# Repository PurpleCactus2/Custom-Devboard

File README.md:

# Custom-Devboard
An RP2040 devboard meant for a completely custom and streamlined electronics development experience!

## Introduction
This is a completely custom devboard made with the wonderful guide by [@Kai Pereira](https://blueprint.hackclub.com/starter-projects/devboard)

It features:

- An RP2040 microcontroller
- All 30 GPIO pins of the RP2040 broken out, with plently power and debugging pins as well
- 2MB of flash storage

## PCB and Schematic

### Schematic
My schematic uses a mostly similar layout to the one suggested in the guide, however, I have also included a diode and VSYS pin so that you can connect an external battery/power source to power the board. In addition to this, I have also changed the external pin layout a little in a way that makes more sense to me, but you'll see what I mean.

Here are a couple of screenshots of the schematic:

The RP2040 with its decoupling capacitors:<br>
<br>

The USB-C port (you can also see the diode I added here):<br>
<br>

The flash memory along with the BOOTSEL button:<br>
<br>

The 12MHz crystal oscillator:<br>
<br>

The IO pins with a slightly changed layout:<br>
<br>

### PCB
This is my first time using SMD so my layout and routing are a little atrocious. But I have tried my best to keep everything as logical as possible.

Here are a couple screenshots of the PCB:

The RP2040 footprint with decoupling caps, crystal and flash:<br>
<br>

The whole board:<br>
<br>

Final render:<br>
<br>

## BOM
|  | Item | Qty | Supplier | Cost/item | Total Cost | link |
|---|---|---|---|---|---|---|
|  | RP2040 | 1 | LCSC | $1.10 | $1.10 | [LCSC](https://www.lcsc.com/product-detail/C2040.html) |
|  | MCP1700 | 1 | LCSC | $0.44 | $0.44 | [LCSC](https://www.lcsc.com/product-detail/C39051.html) |
|  | Crystal | 1 | LCSC | $0.46 | $0.46 | [LCSC](https://www.lcsc.com/product-detail/C9002.html) |
|  | Flash memory | 1 | LCSC | $1.92 | $1.92 | [LCSC](https://www.lcsc.com/product-detail/C2456208.html) |
|  | Button | 1 | LCSC | $0.51 | $0.51 | [LCSC](https://www.lcsc.com/product-detail/C720477.html) |
|  | USB-C Port | 1 | LCSC | $0.87 | $0.87 | [LCSC](https://www.lcsc.com/product-detail/C165948.html) |
|  | Passive Components | 1 | LCSC | $1.57 | $1.57 | [100nF](https://www.lcsc.com/product-detail/C1525.html) [1uF](https://www.lcsc.com/product-detail/C2803380.html) [10uF](https://www.lcsc.com/product-detail/C1691.html) [33pF](https://www.lcsc.com/product-detail/C107005.html) [Diode](https://www.lcsc.com/product-detail/C49231016.html) [5.1KΩ](https://www.lcsc.com/product-detail/C2906874.html) [27Ω](https://www.lcsc.com/product-detail/C2909343.html) [1KΩ](https://www.lcsc.com/product-detail/C2906899.html) [10KΩ](https://www.lcsc.com/product-detail/C2906861.html) |
|  | PCB | 1 | JLCPCB | $4.10 | $4.10 | [LCSC](https://cart.jlcpcb.com/quote?stencilLayer=2&stencilWiddth=100&stencilLength=100&stencilCounts=5&plateType=1&spm=Jlcpcb.Homepage.1010) |
|  | Estimated total shipping |  |  |  | $18.94 |  |
|  | Total |  |  |  | $29.91 |  |

*I am willing to cover any extra charges that might apply*

### Cart Screenshots

LCSC Order:<br>
<br>
<br>
<br>

JLCPCB Order:<br>

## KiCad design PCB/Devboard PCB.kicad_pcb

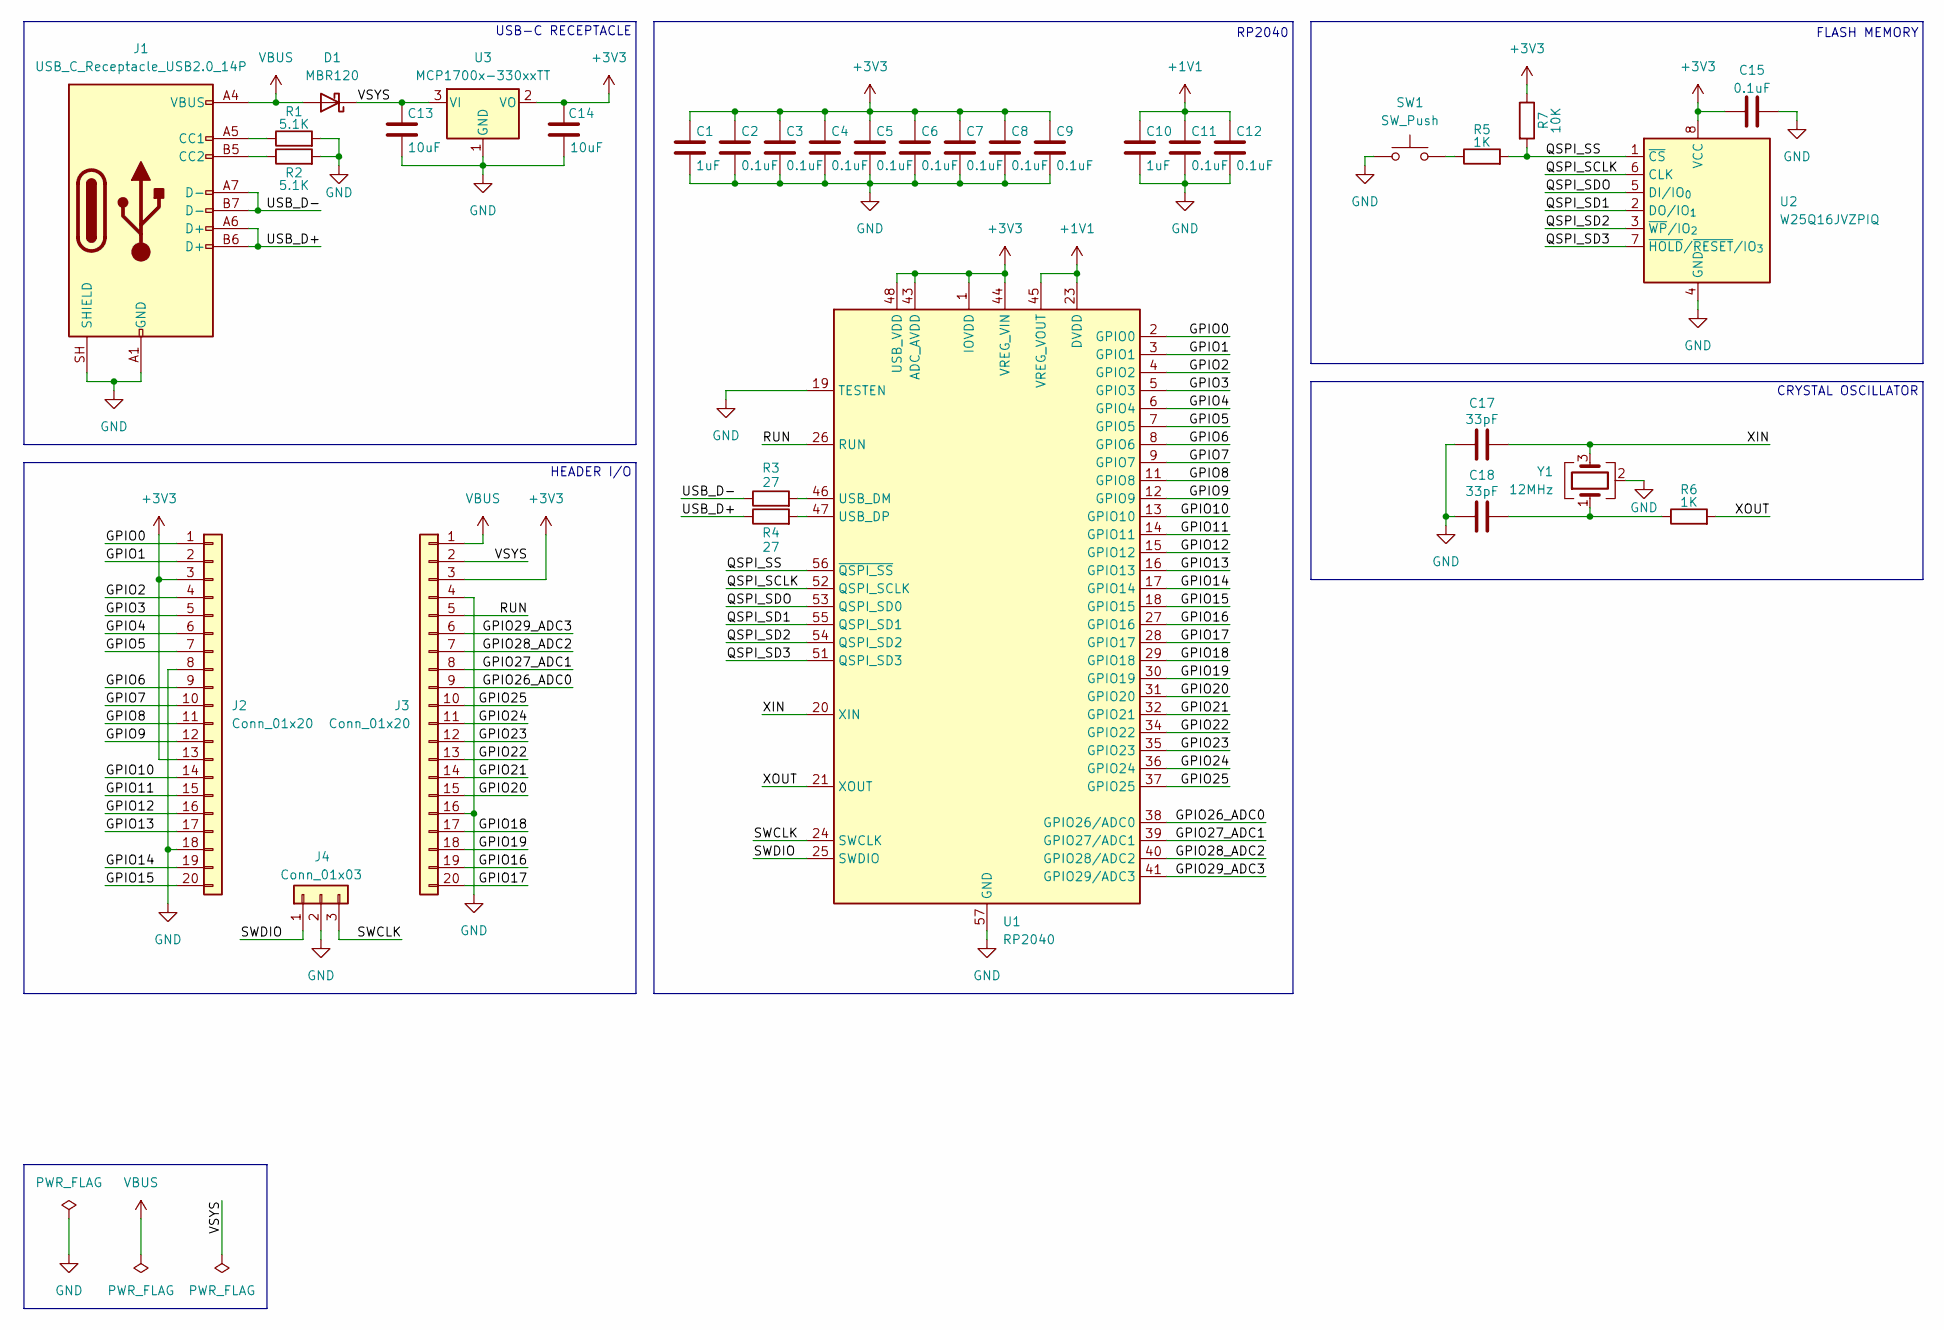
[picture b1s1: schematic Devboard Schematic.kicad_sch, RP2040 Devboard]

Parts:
C1, C10: 1uF; C_0402_1005Metric
C2, C3, C4, C5, C6, C7, C8, C9, C11, C12, C15: 0.1uF; C_0402_1005Metric
C13, C14: 10uF; C_0603_1608Metric
C17, C18: 33pF; C_0402_1005Metric
D1: MBR120; D_SOD-123F
J1: USB_C_Receptacle_USB2.0_14P; USB_C_Receptacle_HRO_TYPE-C-31-M-12
J2, J3: Conn_01x20; PinHeader_1x20_P2.54mm_Vertical
J4: Conn_01x03; PinHeader_1x03_P2.54mm_Vertical
R1, R2: 5.1K; R_01005_0402Metric
R3, R4: 27; R_01005_0402Metric
R5, R6: 1K; R_01005_0402Metric
R7: 10K; R_01005_0402Metric
SW1: SW_Push; SW_Push_SPST_NO_Alps_SKRK
U1: RP2040; QFN-56-1EP_7x7mm_P0.4mm_EP3.2x3.2mm
U2: W25Q16JVZPIQ; Winbond_USON-8-1EP_3x2mm_P0.5mm_EP0.2x1.6mm
U3: MCP1700x-330xxTT; SOT-23
Y1: 12MHz; Crystal_SMD_3225-4Pin_3.2x2.5mm

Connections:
+1V1: C10.1, C11.1, C12.1, U1.23 (DVDD), U1.45 (VREG_VOUT), U1.50 (DVDD)
+3V3: C1.1, C2.1, C3.1, C4.1, C5.1, C6.1, C7.1, C8.1, C9.1, C14.1, C15.1, J2.3, J2.13, J3.3, R7.1, U1.1 (IOVDD), U1.10 (IOVDD), U1.22 (IOVDD), U1.33 (IOVDD), U1.42 (IOVDD), U1.43 (ADC_AVDD), U1.44 (VREG_VIN), U1.48 (USB_VDD), U1.49 (IOVDD), U2.8 (VCC), U3.2 (VO)
/GPIO0: J2.1, U1.2 (GPIO0)
/GPIO1: J2.2, U1.3 (GPIO1)
/GPIO2: J2.4, U1.4 (GPIO2)
/GPIO3: J2.5, U1.5 (GPIO3)
/GPIO4: J2.6, U1.6 (GPIO4)
/GPIO5: J2.7, U1.7 (GPIO5)
/GPIO6: J2.9, U1.8 (GPIO6)
/GPIO7: J2.10, U1.9 (GPIO7)
/GPIO8: J2.11, U1.11 (GPIO8)
/GPIO9: J2.12, U1.12 (GPIO9)
/GPIO10: J2.14, U1.13 (GPIO10)
/GPIO11: J2.15, U1.14 (GPIO11)
/GPIO12: J2.16, U1.15 (GPIO12)
/GPIO13: J2.17, U1.16 (GPIO13)
/GPIO14: J2.19, U1.17 (GPIO14)
/GPIO15: J2.20, U1.18 (GPIO15)
/GPIO16: J3.19, U1.27 (GPIO16)
/GPIO17: J3.20, U1.28 (GPIO17)
/GPIO18: J3.17, U1.29 (GPIO18)
/GPIO19: J3.18, U1.30 (GPIO19)
/GPIO20: J3.15, U1.31 (GPIO20)
/GPIO21: J3.14, U1.32 (GPIO21)
/GPIO22: J3.13, U1.34 (GPIO22)
/GPIO23: J3.12, U1.35 (GPIO23)
/GPIO24: J3.11, U1.36 (GPIO24)
/GPIO25: J3.10, U1.37 (GPIO25)
/GPIO26_ADC0: J3.9, U1.38 (GPIO26/ADC0)
/GPIO27_ADC1: J3.8, U1.39 (GPIO27/ADC1)
/GPIO28_ADC2: J3.7, U1.40 (GPIO28/ADC2)
/GPIO29_ADC3: J3.6, U1.41 (GPIO29/ADC3)
/QSPI_SCLK: U1.52 (QSPI_SCLK), U2.6 (CLK)
/QSPI_SD1: U1.55 (QSPI_SD1), U2.2 (DO/IO_{1})
/QSPI_SD2: U1.54 (QSPI_SD2), U2.3 (~WP/IO_{2})
/QSPI_SD3: U1.51 (QSPI_SD3), U2.7 (~HOLD/~RESET/IO_{3})
/QSPI_SDO: U1.53 (QSPI_SD0), U2.5 (DI/IO_{0})
/QSPI_SS: R5.2, R7.2, U1.56 (~QSPI_SS), U2.1 (~CS)
/RUN: J3.5, U1.26 (RUN)
/SWCLK: J4.3, U1.24 (SWCLK)
/SWDIO: J4.1, U1.25 (SWDIO)
/USB_D+: J1.A6 (D+), J1.B6 (D+), R4.1
/USB_D-: J1.A7 (D-), J1.B7 (D-), R3.1
/VSYS: C13.1, D1.1 (K), J3.2, U3.3 (VI)
/XIN: C17.2, U1.20 (XIN), Y1.3
/XOUT: R6.2, U1.21 (XOUT)
GND: C1.2, C2.2, C3.2, C4.2, C5.2, C6.2, C7.2, C8.2, C9.2, C10.2, C11.2, C12.2, C13.2, C14.2, C15.2, C17.1, C18.1, J1.A1 (GND), J1.A12 (GND), J1.B1 (GND), J1.B12 (GND), J1.SH (SHIELD), J2.8, J2.18, J3.4, J3.16, J4.2, R1.2, R2.2, SW1.1, U1.19 (TESTEN), U1.57 (GND), U2.4 (GND), U3.1 (GND), Y1.2 (G), Y1.4 (G)
unnamed: C18.2, R6.1, Y1.1
unnamed: J1.A5 (CC1), R1.1
unnamed: J1.B5 (CC2), R2.1
unnamed: R5.1, SW1.2
unnamed: R3.2, U1.46 (USB_DM)
unnamed: R4.2, U1.47 (USB_DP)
VBUS: D1.2 (A), J1.A4 (VBUS), J1.A9 (VBUS), J1.B4 (VBUS), J1.B9 (VBUS), J3.1

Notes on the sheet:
USB-C RECEPTACLE
HEADER I/O
RP2040
CRYSTAL OSCILLATOR
FLASH MEMORY

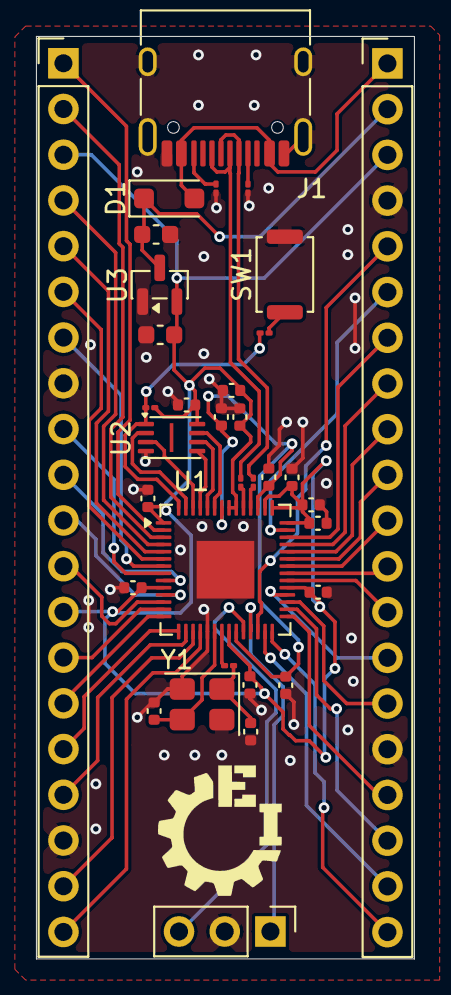
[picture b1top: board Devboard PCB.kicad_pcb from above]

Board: 2 copper layers, 21.0 x 51.2 mm, 34 parts (0 on the bottom side), 54 nets.
